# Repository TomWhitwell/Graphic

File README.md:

# Graphic

A simple, compact and high quality seven band graphic equaliser for Eurorack. Inspired by the Boss GE-7 pedal, but with pristine low-noise circuitry and a much broader frequency range. Simple (if repetitive) SMD soldering with human-sized components. 

Bolder DIYers can easily modify the frequency bands by swapping resistors and capacitors. 

The 5 x N5532 chips draw 7.8ma each (which is in line with the datasheet) = 39ma. They do get quite warm, which seems not abnormal for this chip - you can feel the warmth on the panel! 

With 2k resistors, the 7xLEDs draw  about 38ma making a total of 77ma, which seems quite high compared with simpler circuits using a couple of low-draw Op Amps like the TL072. This circuit will probably work fine with TL072, which would use 14ma (making a total of 52ma) but risks being more noisy. (Now I understand why battery-powered stompboxes like the GE-7 are designed in a way that leaves them rather noisy... )

The PCB panel includes two holes for M2 x 6mm bolts (48SM006) to make the constuction stronger. Place a 3mm spacer between the panel and the slider. 

This m2 x 2.9mm spacer should work: 710-9774015243R, and thisthis M2.5 x 3mm 761-M0502-25-AL should also work OK. 

## Notes on assembling the boards with SMD pre-populated: 
1. There are only two types of parts to attach: Sliders and Sockets.  
1. First, position the sliders. They have 4 pins on one end, 2 pins on the other, so it's impossible to get them the wrong way around. Carefully straighten the pins a little if they don't fit into the holes. I find it easier to insert the 2 pin side first, then slide the 4 pins into place. 
1. Position all the sliders before starting to solder, making sure they're completely even and flat. 
1. Soldering the sliders is simple, but this is a dense board, and you are soldering on the same side as the small surface mount components. In a few places - for example close to the unpopulated C32 - it is very tight. Be careful not to connect the empty solder pads of C32 to the pins, as this will cause strangeness.
1. When soldering the sliders, all the pins should the same length; if you see some that are a bit short, check they're properly pushed through. Otherwise the solders won't be flat and even. 
1. Check all the slider joints - if you miss a connection you can get weird intermittent issues that are hard to debug. 
1. Once the sliders are done, put the sockets in place, then put the front panel on. Ensure the Input socket is at the bottom and the output socket is at the top. Losely tighten the bolts and make sure it all looks right before soldering the three points on the back of each socket.

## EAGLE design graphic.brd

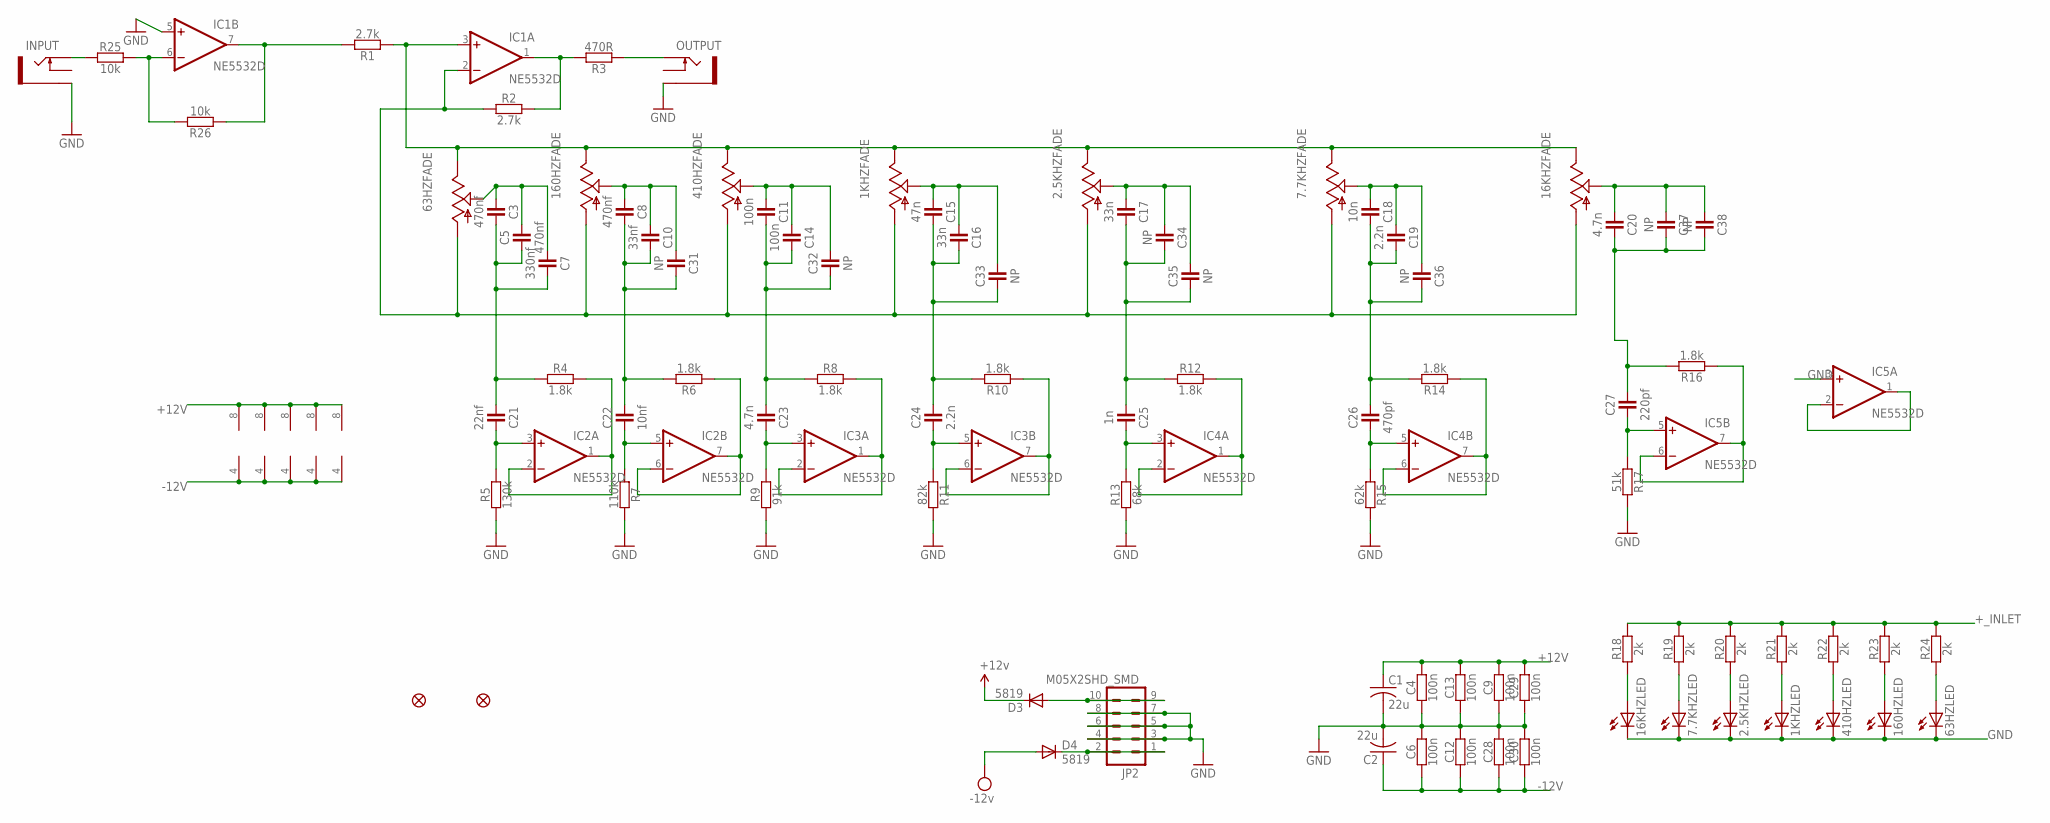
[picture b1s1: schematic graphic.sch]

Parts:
1KHZ, 2.5KHZ, 7.7KHZ, 16KHZ, 63HZ, 160HZ, 410HZ: ALPHA_20MM_ILLUM_FADER; ALPHA_ILL_FADER_20MM_REV2
C1, C2: 22u; C1206
C3, C5, C8: 470nf; C0805
C4, C6, C9, C11, C12, C13, C14, C28, C29, C30: 100n; C0805
C7: 330nf; C0805
C10: 33nf; C0805
C15: 47n; C0805
C16, C17: 33n; C0805
C18: 10n; C0805
C19, C24: 2.2n; C0805
C20, C23: 4.7n; C0805
C21: 22nf; C0805
C22: 10nf; C0805
C25: 1n; C0805
C26: 470pf; C0805
C27: 220pf; C0805
C31, C32, C33, C34, C35, C36, C37, C38: NP; C0805
D3, D4: 5819; SOD123
FID1, FID2: FIDUCIAL1.5X3; FIDUCIAL-1.5X3
IC1, IC2, IC3, IC4, IC5: NE5532D; SO08
INPUT: THONKICONNNEW; WQP-PJ301M-12_JACK
JP2: M05X2SHD_SMD; 2X5-SHROUDED_SMD
OUTPUT: THONKICONNNEW; WQP-PJ301M-12_JACK
R1, R2: 2.7k; C0805
R3: 470R; C0805
R4, R6, R8, R10, R12, R14, R16: 1.8k; C0805
R5: 130k; C0805
R7: 110k; C0805
R9: 91k; C0805
R11: 82k; C0805
R13: 68k; C0805
R15: 62k; C0805
R17: 51k; C0805
R18, R19, R20, R21, R22, R23, R24: 2k; C0805
R25, R26: 10k; C0805

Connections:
+12V: C1.1, C4.2, C9.2, C13.2, C29.2, D3.C, IC1.8 (V+), IC2.8 (V+), IC3.8 (V+), IC4.8 (V+), IC5.8 (V+)
+_INLET: D3.A, JP2.9, JP2.10, R18.2, R19.2, R20.2, R21.2, R22.2, R23.2, R24.2
-12V: C2.1, C6.1, C12.1, C28.1, C30.1, D4.A, IC1.4 (V-), IC2.4 (V-), IC3.4 (V-), IC4.4 (V-), IC5.4 (V-)
-_INLET: D4.C, JP2.1, JP2.2
GND: 1KHZ.E (C), 2.5KHZ.E (C), 7.7KHZ.E (C), 16KHZ.E (C), 63HZ.E (C), 160HZ.E (C), 410HZ.E (C), C1.2, C2.2, C4.1, C6.2, C9.1, C12.2, C13.1, C28.2, C29.1, C30.2, IC1.5 (+IN), IC5.3 (+IN), INPUT.P$3_SLEEVE (SLEEVE), JP2.3, JP2.4, JP2.5, JP2.6, JP2.7, JP2.8, OUTPUT.P$3_SLEEVE (SLEEVE), R5.1, R7.2, R9.1, R11.2, R13.1, R15.2, R17.2
unnamed: INPUT.P$1_TIP (TIP), R25.1
unnamed: 1KHZ.3 (A), 2.5KHZ.3 (A), 7.7KHZ.3 (A), 16KHZ.3 (A), 63HZ.3 (A), 160HZ.3 (A), 410HZ.3 (A), IC1.2 (-IN), R2.1
unnamed: 410HZ.2 (S), C11.1, C14.1, C32.2
unnamed: IC1.1 (OUT), R2.2, R3.2
unnamed: OUTPUT.P$1_TIP (TIP), R3.1
unnamed: 1KHZ.1 (E), 2.5KHZ.1 (E), 7.7KHZ.1 (E), 16KHZ.1 (E), 63HZ.1 (E), 160HZ.1 (E), 410HZ.1 (E), IC1.3 (+IN), R1.1
unnamed: 63HZ.2 (S), C3.1, C5.2, C7.1
unnamed: IC1.6 (-IN), R25.2, R26.2
unnamed: 16KHZ.B (A), R18.1
unnamed: 2.5KHZ.2 (S), C17.1, C34.1, C35.2
unnamed: 1KHZ.2 (S), C15.1, C16.1, C33.2
unnamed: 7.7KHZ.B (A), R19.1
unnamed: 160HZ.2 (S), C8.1, C10.1, C31.1
unnamed: 2.5KHZ.B (A), R20.1
unnamed: C23.2, IC3.3 (+IN), R9.2
unnamed: C3.2, C5.1, C7.2, C21.1, R4.1
unnamed: C8.2, C10.2, C22.2, C31.2, R6.2
unnamed: 7.7KHZ.2 (S), C18.1, C19.1, C36.1
unnamed: 1KHZ.B (A), R21.1
unnamed: IC3.1 (OUT), IC3.2 (-IN), R8.2
unnamed: IC5.1 (OUT), IC5.2 (-IN)
unnamed: 16KHZ.2 (S), C20.1, C37.1, C38.1
unnamed: C24.1, IC3.5 (+IN), R11.1
unnamed: C21.2, IC2.3 (+IN), R5.2
unnamed: IC2.1 (OUT), IC2.2 (-IN), R4.2
unnamed: IC3.6 (-IN), IC3.7 (OUT), R10.1
unnamed: C22.1, IC2.5 (+IN), R7.1
unnamed: IC2.6 (-IN), IC2.7 (OUT), R6.1
unnamed: C11.2, C14.2, C23.1, C32.1, R8.1
unnamed: C15.2, C16.2, C24.2, C33.1, R10.2
unnamed: C25.2, IC4.3 (+IN), R13.2
unnamed: IC4.1 (OUT), IC4.2 (-IN), R12.2
unnamed: C26.1, IC4.5 (+IN), R15.1
unnamed: IC4.6 (-IN), IC4.7 (OUT), R14.1
unnamed: C17.2, C25.1, C34.2, C35.1, R12.1
unnamed: C18.2, C19.2, C26.2, C36.2, R14.2
unnamed: C27.1, IC5.5 (+IN), R17.1
unnamed: IC5.6 (-IN), IC5.7 (OUT), R16.1
unnamed: C20.2, C27.2, C37.2, C38.2, R16.2
unnamed: 410HZ.B (A), R22.1
unnamed: 160HZ.B (A), R23.1
unnamed: 63HZ.B (A), R24.1
unnamed: IC1.7 (OUT), R1.2, R26.1

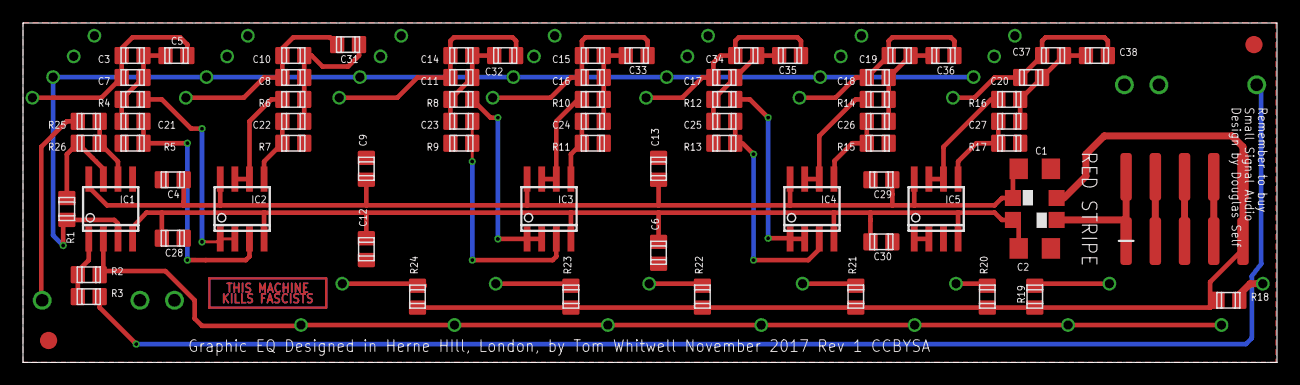
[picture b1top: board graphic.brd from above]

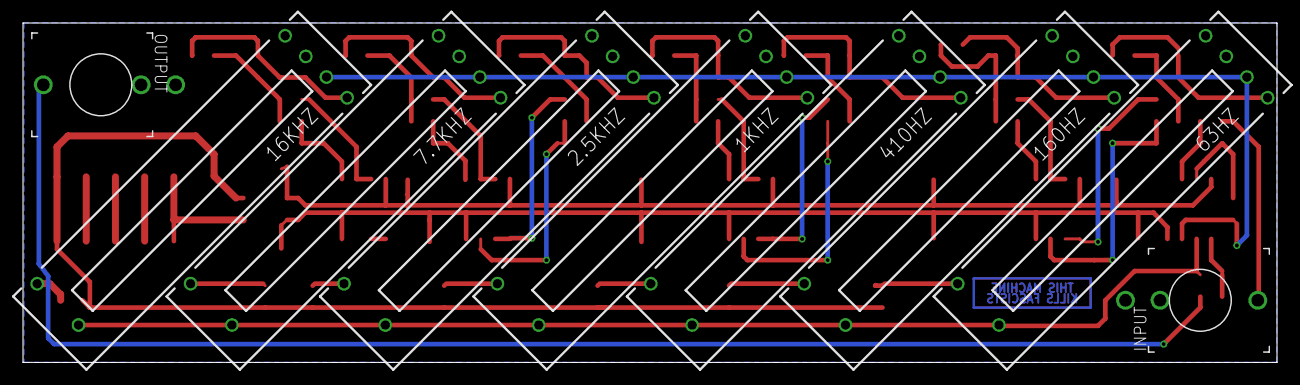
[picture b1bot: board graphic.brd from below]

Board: 2 copper layers, 109.0 x 29.5 mm, 84 parts (9 on the bottom side), 48 nets.

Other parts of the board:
U$1: TMKF

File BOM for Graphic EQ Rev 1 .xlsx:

Manufacturer | Manufacturer Part Number | Designator | Qty | Description | Case | SMD ,BGA,LCC,OR TH | Top/Bottom | points | Total points | Comment
Murata | GRM31CR61C226KE15L | C1, C2 | 2.0 | 22u C-USC1206 | C1206 | SMD | TOP | 1 | Murata | GRM31CR61C226KE15L | C1, C2 | 2.0 | 22uF,16V,10%,X5R,1206 | 1206 | SMD | Top | 2.0 | 4
Murata | GRM219R71H333KA01D | C10, C16, C17 | 3.0 | 33nf CAPACITOR-0805 | C0805 | SMD | TOP | 1 | Murata | GRM219R71H333KA01D | C10, C16, C17 | 3.0 | 33nF,50V,10%,X7R,0805 | 0805 | SMD | Top | 2.0 | 6
Murata | GCM21BR72A104KA37L | C11, C14, C4, C6, C9, C12, C13, C28, C29, C30 | 10.0 | 100n CAPACITOR-0805 | C0805 | SMD | TOP | 1 | Murata | GCM21BR72A104KA37L | C11, C14, C4, C6, C9, C12, C13, C28, C29, C30 | 10.0 | 100nF,100V,10%,X7R,0805 | 0805 | SMD | Top | 2.0 | 20
Murata | GRM21BR71H473KA01L | C15 | 1.0 | 47n CAPACITOR-0805 | C0805 | SMD | TOP | 1 | Murata | GRM21BR71H473KA01L | C15 | 1.0 | 47nF,50V,10%,X7R,0805 | 0805 | SMD | Top | 2.0 | 2
Murata | GRM216R71H103KA01D | C18, C22 | 2.0 | 10n CAPACITOR-0805 | C0805 | SMD | TOP | 1 | Murata | GRM216R71H103KA01D | C18, C22 | 2.0 | 10nF,50V,10%,X7R,0805 | 0805 | SMD | Top | 2.0 | 4
Murata | GRM216R71H222KA01D | C19, C24 | 2.0 | 2.2n CAPACITOR-0805 | C0805 | SMD | TOP | 1 | Murata | GRM216R71H222KA01D | C19, C24 | 2.0 | 2.2nF,50V,10%,X7R,0805 | 0805 | SMD | Top | 2.0 | 4
Murata | GRM216R71H472KA01D | C20, C23 | 2.0 | 4.7n CAPACITOR-0805 | C0805 | SMD | TOP | 1 | Murata | GRM216R71H472KA01D | C20, C23 | 2.0 | 4.7nF,50V,10%,X7R,0805 | 0805 | SMD | Top | 2.0 | 4
Murata | GRM216R71H223KA01D | C21 | 1.0 | 22nf CAPACITOR-0805 | C0805 | SMD | TOP | 1 | Murata | GRM216R71H223KA01D | C21 | 1.0 | 22nF,50V,10%,X7R,0805 | 0805 | SMD | Top | 2.0 | 2
Murata | GRM216R71H102KA01D | C25 | 1.0 | 1n CAPACITOR-0805 | C0805 | SMD | TOP | 1 | Murata | GRM216R71H102KA01D | C25 | 1.0 | 1nF,50V,10%,X7R,0805 | 0805 | SMD | Top | 2.0 | 2
Murata | GRM216R71H471KA01D | C26 | 1.0 | 470pf CAPACITOR-0805 | C0805 | SMD | TOP | 1 | Murata | GRM216R71H471KA01D | C26 | 1.0 | 470pF,50V,10%,X7R,0805 | 0805 | SMD | Top | 2.0 | 2
Murata | GRM216R71H221KA01D | C27 | 1.0 | 220pf CAPACITOR-0805 | C0805 | SMD | TOP | 1 | Murata | GRM216R71H221KA01D | C27 | 1.0 | 220pF,50V,10%,X7R,0805 | 0805 | SMD | Top | 2.0 | 2
Murata | GRM21BR71H474KA88L | C3, C5, C8 | 3.0 | 470nf CAPACITOR-0805 | C0805 | SMD | TOP | 1 | Murata | GRM21BR71H474KA88L | C3, C5, C8 | 3.0 | 470nF,50V,10%,X7R,0805 | 0805 | SMD | Top | 2.0 | 6
 |  | C31, C32, C33, C34, C35, C36, C37, C38 | 8.0 | DO NOT POPULATE | C0805 | SMD | TOP | 1
Murata | GRM21BR71C334KA01L | C7 | 1.0 | 330nf CAPACITOR-0805 | C0805 | SMD | TOP | 1 | Murata | GRM21BR71C334KA01L | C7 | 1.0 | 330nF,16V,10%,X7R,0805 | 0805 | SMD | Top | 2.0 | 2
Diodes Inc | 621-1N5819HW-F | D3, D4 | 2.0 | 5819 DIODE-SOD123 | SOD123 | SMD | TOP | 0 | Diodes Incorporated | 1N5819HW-7-F | D3, D4 | 2.0 | 40V,1A,SOD-123 | SOD-123 | SMD | Top | 2.0 | 4
Texas Instruments | NE5532DR | IC1, IC2, IC3, IC4, IC5 | 5.0 | NE5532D NE5532D | SO08 | SMD | TOP | 1 | Texas Instruments | NE5532DR | IC1, IC2, IC3, IC4, IC5 | 5.0 | NE5532DR,SOIC-8 | SOIC-8 | SMD | Top | 8.0 | 40
Molex | 15-91-2100 | JP2 | 1.0 | M05X2SHD_SMD M05X2SHD_SMD | 2X5-SHROUDED_SMD | SMD | TOP | 1 | Molex | 15-91-2100 | JP2 | 1.0 | 2*5pin, pitches2.54mm,180° | pitches2.54mm | SMD | Top | 10.0 | 10
Yageo | RC0805FR-072K7L | R1, R2 | 2.0 | 2.7k RESISTOR-0805 | C0805 | SMD | TOP | 1 | Yageo | RC0805FR-072K7L | R1, R2 | 2.0 | 2.7K,1%,1/8W,0805 | 0805 | SMD | Top | 2.0 | 4
Yageo | RC0805FR-0782KL | R11 | 1.0 | 82k RESISTOR-0805 | C0805 | SMD | TOP | 1 | Yageo | RC0805FR-0782KL | R11 | 1.0 | 82K,1%,1/8W,0805 | 0805 | SMD | Top | 2.0 | 2
Yageo | RC0805FR-0768KL | R13 | 1.0 | 68k RESISTOR-0805 | C0805 | SMD | TOP | 1 | Yageo | RC0805FR-0768KL | R13 | 1.0 | 68K,1%,1/8W,0805 | 0805 | SMD | Top | 2.0 | 2
Yageo | RC0805FR-0762KL | R15 | 1.0 | 62k RESISTOR-0805 | C0805 | SMD | TOP | 1 | Yageo | RC0805FR-0762KL | R15 | 1.0 | 62K,1%,1/8W,0805 | 0805 | SMD | Top | 2.0 | 2
Yageo | RC0805FR-0751KL | R17 | 1.0 | 51k RESISTOR-0805 | C0805 | SMD | TOP | 1 | Yageo | RC0805FR-0751KL | R17 | 1.0 | 51K,1%,1/8W,0805 | 0805 | SMD | Top | 2.0 | 2
Yageo | RC0805FR-072KL | R18, R19, R20, R21, R22, R23, R24 | 7.0 | 2k RESISTOR-0805 | C0805 | SMD | TOP | 1 | Yageo | RC0805FR-072KL | R18, R19, R20, R21, R22, R23, R24 | 7.0 | 2K,1%,1/8W,0805 | 0805 | SMD | Top | 2.0 | 14
Yageo | RC0805FR-0710KL | R25, R26 | 2.0 | 10k RESISTOR-0805 | C0805 | SMD | TOP | 1 | Yageo | RC0805FR-0710KL | R25, R26 | 2.0 | 10K,1%,1/8W,0805 | 0805 | SMD | Top | 2.0 | 4
Yageo | RC0805FR-07470RL | R3 | 1.0 | 470R RESISTOR-0805 | C0805 | SMD | TOP | 1 | Yageo | RC0805FR-07470RL | R3 | 1.0 | 470R,1%,1/8W,0805 | 0805 | SMD | Top | 2.0 | 2
Yageo | RC0805FR-071K8L | R4, R6, R8, R10, R12, R14, R16 | 7.0 | 1.8k RESISTOR-0805 | C0805 | SMD | TOP | 0 | Yageo | RC0805FR-071K8L | R4, R6, R8, R10, R12, R14, R16 | 7.0 | 1.8K,1%,1/8W,0805 | 0805 | SMD | Top | 2.0 | 14
Yageo | RC0805FR-07130KL | R5 | 1.0 | 130k RESISTOR-0805 | C0805 | SMD | TOP | 0 | Yageo | RC0805FR-07130KL | R5 | 1.0 | 130K,1%,1/8W,0805 | 0805 | SMD | Top | 2.0 | 2
Yageo | RC0805FR-07110KL | R7 | 1.0 | 110k RESISTOR-0805 | C0805 | SMD | TOP | 0 | Yageo | RC0805FR-07110KL | R7 | 1.0 | 110K,1%,1/8W,0805 | 0805 | SMD | Top | 2.0 | 2
Yageo | RC0805FR-0791KL | R9 | 1.0 | 91k RESISTOR-0805 | C0805 | SMD | TOP | 0 | Yageo | RC0805FR-0791KL | R9 | 1.0 | 91K,1%,1/8W,0805 | 0805 | SMD | Top | 2.0 | 2

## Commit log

2017-01-26 Initial upload
2017-01-27 Simple version PCB complete and routed
2017-01-28 Creating experimental stereo output versions
2017-01-30 Prototype 1 sent to OSHPark
2017-02-12 updated 20mm fader outlines - NOT moved yet
2017-02-12 move sliders and reverse movement
2017-02-16 re route and redesign panel
2017-03-18 Updated illuminated fader outline
2017-05-11 rev 3 Panel Gerbers
2017-05-25 test
2017-05-29 Increase LED resistors to reduce current draw
2017-06-10 Remove non-working stereo experiments
2017-08-30 Add schematic + update
2017-08-30 Revert "Merge branch 'fix-panel'"
    This reverts commit 24303b16601d2e124062e02205cddf4c546a9bcf, reversing
    changes made to eef96a0ff0da711b8061c4b766c52a963260b08f.
2017-08-30 add schematic
2017-09-26 Tweaks for Rev 1 boards: improve ground plane clearance, move one resistor, move Kills Fascists arwork, small changes to get ground plane to work
2017-11-15 Revert "Tweaks for Rev 1 boards: improve ground plane clearance, move one resistor, move Kills Fascists arwork, small changes to get ground plane to work"
    This reverts commit c469b6aed1205b33f2cf1fbab66cd5b8357eaae7.
2017-11-15 Revision 1 board finalised - moved one resistor + added Fiducials
2022-05-10 Add BOM

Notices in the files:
parts and their libraries:
SparkFun-Connectors: Licensing: CC v3.0 Share-Alike You are welcome to use this library for commercial purposes.
